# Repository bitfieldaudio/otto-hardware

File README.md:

# Description
otto-hw-beta is the hardware design for the OTTO beta circuit board. The design is implemented in KiCad.

# Target Outputs
By Beta formal release, the target output files will be the following:
Schematic
Layout
Fabrication Gerber
	Copper Layers
	Soldermask
	Silkscreen
	Drill
Assembly Gerber
	Paste Mask
	Component/Pin-XY Data
Bill of Materials
	Installed/Not-Installed
	Part Numbers
	Purchase Reference links
	Est. Cost

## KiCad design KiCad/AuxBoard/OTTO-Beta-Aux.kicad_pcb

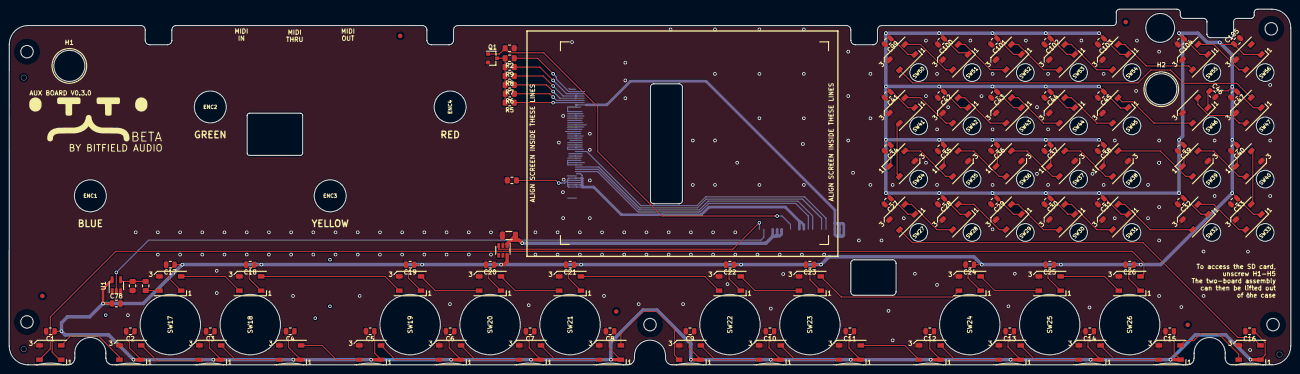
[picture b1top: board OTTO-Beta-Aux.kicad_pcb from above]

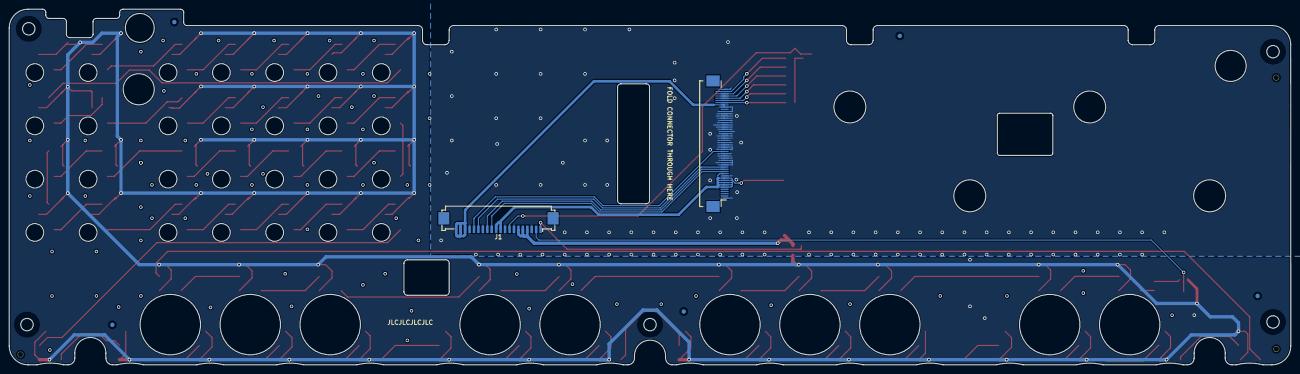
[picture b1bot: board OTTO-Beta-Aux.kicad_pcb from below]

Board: 2 copper layers, 288.5 x 80.1 mm, 187 parts (6 on the bottom side), 74 nets.

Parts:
C1, C2, C3, C4, C5, C6, C7, C8, C9, C10, C11, C12, C13, C14, C15, C16, C17, C18, C19, C20, C21, C22, C23, C24, C25, C26, C27, C28, C29, C30, C31, C32, C33, C34, C35, C36, C37, C38, C39, C40, C41, C42, C43, C44, C45, C46, C47, C78, C99, C100, C101, C102, C103, C104, C105: 100nF; C_0805_2012Metric
C48: 100nF; C_0805_2012Metric_Pad1.15x1.40mm_HandSolder
C49: 47uF; C_1206_3216Metric
ENC1, ENC2, ENC3, ENC4: ALPS EC11 HOLE; ALPS_EC11_aux_hole
FID2, FID3, FID4, FID5, FID6, FID8, FID9, FID10, FID11, FID12: Fiducial; Fiducial_1mm_Mask2mm
H1, H2: MountingHole_Pad; MountingHoleHole
H101, H102, H103: Tooling Hole; JLC_TOOLING_HOLE
H201, H202, H203, H204, H205: MountingHole; Mounting_Hole_M2.5_Loose_Fit
J1: Conn_01x20; X10B25L20T_FPC_1x20-1MP_P1.00mm_Horizontal
J1_KD028QVFMA17: Conn_02x25_Counter_Clockwise; F0501-B-50-20T-R
LED1, LED2, LED3, LED4, LED5, LED6, LED7, LED8, LED9, LED10, LED11, LED12, LED13, LED14, LED15, LED16, LED17, LED18, LED19, LED20, LED21, LED22, LED23, LED24, LED25, LED26, LED27, LED28, LED29, LED30, LED31, LED32, LED33, LED34, LED35, LED36, LED37, LED38, LED39, LED40, LED41, LED42, LED43, LED44, LED45, LED46, LED47, LED48, LED49, LED50, LED51, LED52, LED53, LED54: WS2812C; LED_WS2812B_PLCC4_5.0x5.0mm_P3.2mm
Q1: AO3400A; SOT-23
R1: 47k; R_0805_2012Metric_Pad1.15x1.40mm_HandSolder
R2, R5, R6, R7, R8, R9: 90; R_0805_2012Metric_Pad1.15x1.40mm_HandSolder
R11: 100k; R_0805_2012Metric_Pad1.15x1.40mm_HandSolder
R208: 100; R_0805_2012Metric_Pad1.15x1.40mm_HandSolder
SW17, SW18, SW19, SW20, SW21, SW22, SW23, SW24, SW25, SW26: ALPS SKHC Hole; ALPS_SKHC_aux_hole
SW27, SW28, SW29, SW30, SW31, SW32, SW33, SW34, SW35, SW36, SW37, SW38, SW39, SW40, SW41, SW42, SW43, SW44, SW45, SW46, SW47, SW50, SW51, SW52, SW53, SW54, SW55, SW56: 6x6x13mm Hole; 6x6mm_Switch_aux_hole
U1: SN74LV1T34_SOT-23_A; SOT-23-5_HandSoldering
U2: TPS22918_SOT23-6_A; SOT-23-6

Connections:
3V3: C48.1, J1.10, J1.11, J1_KD028QVFMA17.6, J1_KD028QVFMA17.7, J1_KD028QVFMA17.8, J1_KD028QVFMA17.9, J1_KD028QVFMA17.10, J1_KD028QVFMA17.12
+5V_LEDS: C1.1, C2.1, C3.1, C4.1, C5.1, C6.1, C7.1, C8.1, C9.1, C10.1, C11.1, C12.1, C13.1, C14.1, C15.1, C16.1, C17.1, C18.1, C19.1, C20.1, C21.1, C22.1, C23.1, C24.1, C25.1, C26.1, C27.1, C28.1, C29.1, C30.1, C31.1, C32.1, C33.1, C34.1, C35.1, C36.1, C37.1, C38.1, C39.1, C40.1, C41.1, C42.1, C43.1, C44.1, C45.1, C46.1, C47.1, C78.1, C99.1, C100.1, C101.1, C102.1, C103.1, C104.1, C105.1, LED1.1, LED2.1, LED3.1, LED4.1, LED5.1, LED6.1, LED7.1, LED8.1, LED9.1, LED10.1, LED11.1, LED12.1, LED13.1, LED14.1, LED15.1, LED16.1, LED17.1, LED18.1, LED19.1, LED20.1, LED21.1, LED22.1, LED23.1, LED24.1, LED25.1, LED26.1, LED27.1, LED28.1, LED29.1, LED30.1, LED31.1, LED32.1, LED33.1, LED34.1, LED35.1, LED36.1, LED37.1, LED38.1, LED39.1, LED40.1, LED41.1, LED42.1, LED43.1, LED44.1, LED45.1, LED46.1, LED47.1, LED48.1, LED49.1, LED50.1, LED51.1, LED52.1, LED53.1, LED54.1, U1.5, U2.6
+5V_RASPI: J1.18, J1.19, J1.20, J1_KD028QVFMA17.43
+5V_REG: C49.1, J1.4, J1.5, J1.6, U2.1
/LED_PWR_EN: J1.1, U2.3
/LEDs/LED_CONN1: LED1.4, LED26.2
/LEDs/LED_CONN2: LED16.2, LED27.4
/LEDs/LED_CONN3: LED47.2, LED48.4
/LEDs/LED_IN: LED17.4, R208.1
/LEDs/SPI_MOSI_MCU_5V: R11.1, R208.2, U1.4
/SPI_MOSI_MCU: J1.2, U1.2
BL_PWM: J1.8, Q1.1, R1.2
GND: C1.2, C2.2, C3.2, C4.2, C5.2, C6.2, C7.2, C8.2, C9.2, C10.2, C11.2, C12.2, C13.2, C14.2, C15.2, C16.2, C17.2, C18.2, C19.2, C20.2, C21.2, C22.2, C23.2, C24.2, C25.2, C26.2, C27.2, C28.2, C29.2, C30.2, C31.2, C32.2, C33.2, C34.2, C35.2, C36.2, C37.2, C38.2, C39.2, C40.2, C41.2, C42.2, C43.2, C44.2, C45.2, C46.2, C47.2, C48.2, C49.2, C78.2, C99.2, C100.2, C101.2, C102.2, C103.2, C104.2, C105.2, J1.3, J1.7, J1.9, J1.14, J1.17, J1_KD028QVFMA17.1, J1_KD028QVFMA17.11, J1_KD028QVFMA17.16, J1_KD028QVFMA17.17, J1_KD028QVFMA17.18, J1_KD028QVFMA17.19, J1_KD028QVFMA17.20, J1_KD028QVFMA17.21, J1_KD028QVFMA17.23, J1_KD028QVFMA17.24, J1_KD028QVFMA17.25, J1_KD028QVFMA17.26, J1_KD028QVFMA17.27, J1_KD028QVFMA17.28, J1_KD028QVFMA17.29, J1_KD028QVFMA17.30, J1_KD028QVFMA17.31, J1_KD028QVFMA17.32, J1_KD028QVFMA17.33, J1_KD028QVFMA17.34, J1_KD028QVFMA17.35, J1_KD028QVFMA17.36, J1_KD028QVFMA17.37, J1_KD028QVFMA17.38, J1_KD028QVFMA17.39, J1_KD028QVFMA17.40, J1_KD028QVFMA17.42, J1_KD028QVFMA17.50, LED1.3, LED2.3, LED3.3, LED4.3, LED5.3, LED6.3, LED7.3, LED8.3, LED9.3, LED10.3, LED11.3, LED12.3, LED13.3, LED14.3, LED15.3, LED16.3, LED17.3, LED18.3, LED19.3, LED20.3, LED21.3, LED22.3, LED23.3, LED24.3, LED25.3, LED26.3, LED27.3, LED28.3, LED29.3, LED30.3, LED31.3, LED32.3, LED33.3, LED34.3, LED35.3, LED36.3, LED37.3, LED38.3, LED39.3, LED40.3, LED41.3, LED42.3, LED43.3, LED44.3, LED45.3, LED46.3, LED47.3, LED48.3, LED49.3, LED50.3, LED51.3, LED52.3, LED53.3, LED54.3, Q1.2, R1.1, R11.2, U1.3, U2.2
unnamed: J1_KD028QVFMA17.44, R5.1
unnamed: J1_KD028QVFMA17.45, R6.1
unnamed: J1_KD028QVFMA17.46, R7.1
unnamed: J1_KD028QVFMA17.47, R8.1
unnamed: J1_KD028QVFMA17.48, R9.1
unnamed: J1_KD028QVFMA17.49, R2.1
unnamed: LED1.2, LED2.4
unnamed: LED2.2, LED3.4
unnamed: LED3.2, LED4.4
unnamed: LED4.2, LED5.4
unnamed: LED5.2, LED6.4
unnamed: LED6.2, LED7.4
unnamed: LED7.2, LED8.4
unnamed: LED8.2, LED9.4
unnamed: LED10.2, LED11.4
unnamed: LED9.2, LED10.4
unnamed: LED11.2, LED12.4
unnamed: LED12.2, LED13.4
unnamed: LED13.2, LED14.4
unnamed: LED14.2, LED15.4
unnamed: LED15.2, LED16.4
unnamed: LED17.2, LED18.4
unnamed: LED18.2, LED19.4
unnamed: LED19.2, LED20.4
unnamed: LED20.2, LED21.4
unnamed: LED21.2, LED22.4
unnamed: LED22.2, LED23.4
unnamed: LED23.2, LED24.4
unnamed: LED24.2, LED25.4
unnamed: LED25.2, LED26.4
unnamed: LED27.2, LED28.4
unnamed: LED28.2, LED29.4
unnamed: LED29.2, LED30.4
unnamed: LED30.2, LED31.4
unnamed: LED31.2, LED32.4
unnamed: LED32.2, LED33.4
unnamed: LED33.2, LED40.4
unnamed: LED34.2, LED41.4
unnamed: LED34.4, LED35.2
unnamed: LED35.4, LED36.2
unnamed: LED36.4, LED37.2
unnamed: LED37.4, LED38.2
unnamed: LED38.4, LED39.2
unnamed: LED39.4, LED40.2
unnamed: LED41.2, LED42.4
unnamed: LED42.2, LED43.4
unnamed: LED43.2, LED44.4
unnamed: LED44.2, LED45.4
unnamed: LED45.2, LED46.4
unnamed: LED46.2, LED47.4
unnamed: LED48.2, LED49.4
unnamed: LED49.2, LED50.4
unnamed: LED50.2, LED51.4
unnamed: LED51.2, LED52.4
unnamed: LED52.2, LED53.4
unnamed: LED53.2, LED54.4
unnamed: Q1.3, R2.2, R5.2, R6.2, R7.2, R8.2, R9.2
RESET: J1.12, J1_KD028QVFMA17.13
SPI_CS_RASPI: J1.13, J1_KD028QVFMA17.14
SPI_MOSI_RASPI: J1.16, J1_KD028QVFMA17.22
SPI_SCLK_RASPI: J1.15, J1_KD028QVFMA17.15

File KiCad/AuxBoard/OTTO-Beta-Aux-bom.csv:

Comment,Designator,Footprint,LCSC, AssemblyOption, JLCASM, MPN, LCSC PN
"100nF","C16,C15,C14,C13,C12,C11,C10,C9,C8,C7,C6,C5,C4,C3,C2,C1,C26,C25,C24,C23,C22,C21,C20,C19,C18,C17,C29,C30,C28,C33,C31,C32,C34,C46,C45,C47,C42,C41,C44,C43,C39,C38,C40,C35,C37,C36,C27,C78,C105,C104,C103,C102,C101,C100,C99","Capacitor_SMD:C_0805_2012Metric","","","BASIC","CC0805KRX7R9BB104","C49678"
"100nF","C48","Capacitor_SMD:C_0805_2012Metric_Pad1.15x1.40mm_HandSolder","","","BASIC","CC0805KRX7R9BB104","C49678"
"47uF","C49","Capacitor_SMD:C_1206_3216Metric","","","EXT","CL31A476MQHNNNE","C68361"
"10nF","C50","Capacitor_SMD:C_0805_2012Metric_Pad1.15x1.40mm_HandSolder","","","BASIC","CL21B103KBANNNC","C1710"
"ALPS EC11 HOLE","ENC1,ENC2,ENC4,ENC3","OTTO_Footprints_Lib:ALPS_EC11_aux_hole","","","N/A","N/A",""
"Fiducial","FID2,FID3,FID4,FID5,FID8,FID9,FID10,FID11,FID12,FID6","Fiducial:Fiducial_1mm_Mask2mm","","DNP","N/A","N/A",""
"Tooling Hole","H101,H102,H103","OTTO_Footprints_Lib:JLC_TOOLING_HOLE","","DNP","N/A","N/A",""
"MountingHole_Pad","H2,H1","OTTO_Footprints_Lib:MountingHoleHole","","DNP","N/A","N/A",""
"MountingHole","H201,H203,H205,H204,H202","OTTO_Footprints_Lib:Mounting_Hole_M2.5_Loose_Fit","","DNP","N/A","N/A",""
"Conn_01x20","J1","OTTO_Footprints_Lib:X10B25L20T_FPC_1x20-1MP_P1.00mm_Horizontal","","","DNP","X10B25L20T","C500179"
"Conn_02x25_Counter_Clockwise","J1_KD028QVFMA17","OTTO_Footprints_Lib:F0501-B-50-20T-R","","","DNP","F0501-B-50-20T-R","C481235"
"WS2812C","LED47,LED46,LED45,LED44,LED41,LED42,LED43,LED35,LED34,LED36,LED39,LED38,LED37,LED40,LED27,LED33,LED32,LED31,LED30,LED29,LED28,LED17,LED18,LED19,LED20,LED21,LED22,LED23,LED24,LED25,LED26,LED12,LED11,LED10,LED9,LED16,LED15,LED14,LED13,LED7,LED6,LED5,LED4,LED3,LED2,LED1,LED8,LED48,LED49,LED50,LED51,LED52,LED53,LED54","OTTO_Footprints_Lib:LED_WS2812B_PLCC4_5.0x5.0mm_P3.2mm","","","EXT","WS2812C","C114587"
"AO3400A","Q1","OTTO_Footprints_Lib:SOT-23","","","BASIC","AO3400A","C20917"
"47k","R1","Resistor_SMD:R_0805_2012Metric_Pad1.15x1.40mm_HandSolder","","","BASIC","0805W8F4702T5E","C17713"
"90","R2,R9,R8,R7,R6,R5","Resistor_SMD:R_0805_2012Metric_Pad1.15x1.40mm_HandSolder","","","EXT","0805W8F900JT5E","C247027"
"100","R208","Resistor_SMD:R_0805_2012Metric_Pad1.15x1.40mm_HandSolder","","","BASIC","0805W8F1000T5E","C17408"
"100k","R3,R11","Resistor_SMD:R_0805_2012Metric_Pad1.15x1.40mm_HandSolder","","","BASIC","0805W8F1003T5E","C17407"
"0","R4","Resistor_SMD:R_0805_2012Metric_Pad1.15x1.40mm_HandSolder","","","BASIC","0805W8F0000T5E","C17477"
"ALPS SKHC Hole","SW17,SW1,SW18,SW19,SW20,SW21,SW2,SW22,SW23,SW24,SW25,SW26,SW3,SW4,SW5,SW6,SW7,SW8,SW9,SW10,SW11,SW12,SW13,SW14,SW15,SW16","OTTO_Footprints_Lib:ALPS_SKHC_aux_hole","","","N/A","",""
"6x6x13mm Hole","SW41,SW34,SW27,SW42,SW35,SW28,SW43,SW36,SW29,SW44,SW37,SW30,SW45,SW38,SW31,SW46,SW39,SW32,SW47,SW40,SW33,SW50,SW51,SW52,SW53,SW54,SW55,SW56","OTTO_Footprints_Lib:6x6mm_Switch_aux_hole","","","N/A","",""
"SN74LV1T34_SOT-23_A","U1","OTTO_Footprints_Lib:SOT-23-5_HandSoldering","","","EXT","SN74LV1T34DBVR","C100024"
"TPS22918_SOT23-6_A","U2","OTTO_Footprints_Lib:SOT-23-6","","","EXT","TPS22918DBVR","C131941"

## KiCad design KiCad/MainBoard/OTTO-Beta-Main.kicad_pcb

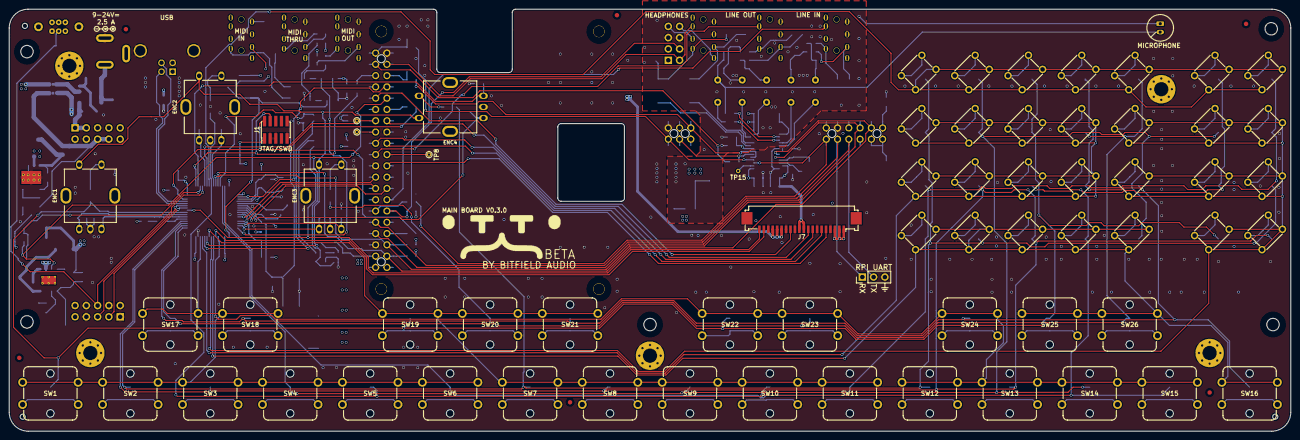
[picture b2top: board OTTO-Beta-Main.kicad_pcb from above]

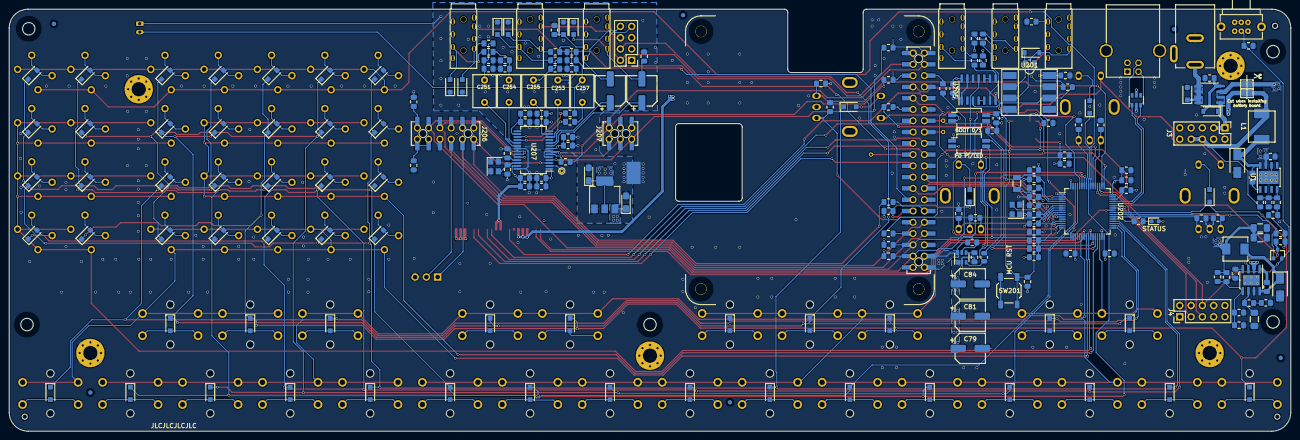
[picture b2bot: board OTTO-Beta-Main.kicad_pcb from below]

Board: 4 copper layers, 288.5 x 95.0 mm, 314 parts (230 on the bottom side), 199 nets.

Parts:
C1, C3, C243, C246, C247, C250, C260, C261, C264: 10uF; C_0805_2012Metric_Pad1.15x1.40mm_HandSolder
C2, C5, C6, C87: 10nF; C_0805_2012Metric_Pad1.15x1.40mm_HandSolder
C4, C7, C48, C49, C50, C51, C52, C53, C54, C55, C60, C61, C62, C63, C64, C65, C66, C67, C68, C69, C70, C71, C72, C73, C74, C98: 100nF; C_0805_2012Metric_Pad1.15x1.40mm_HandSolder
C8: 1nF; C_0805_2012Metric_Pad1.15x1.40mm_HandSolder
C9, C10, C11: 47uF; C_1206_3216Metric_Pad1.42x1.75mm_HandSolder
C79, C81, C84, C258, C262: 220uF; CP_Elec_6.3x4.5
C96, C97: 15pF; C_0805_2012Metric_Pad1.15x1.40mm_HandSolder
C204, C205, C265, C266: 30pF; C_0805_2012Metric_Pad1.15x1.40mm_HandSolder
C211: 4.7uF; C_0805_2012Metric_Pad1.15x1.40mm_HandSolder
C218, C219: 1uF; C_0805_2012Metric_Pad1.15x1.40mm_HandSolder
C251, C253, C254, C255, C257: 1uF (AUDIO); C_Rect_L7.2mm_W5.0mm_P5.00mm_FKS2_FKP2_MKS2_MKP2
C252, C256, C259: 220pF (C0G); C_0805_2012Metric_Pad1.15x1.40mm_HandSolder
C267, C268: 10uf Tantalum; CP_EIA-3216-18_Kemet-A_Pad1.58x1.35mm_HandSolder
D1, D2, D3, D4, D5, D6, D7, D8, D9, D10, D11, D12, D13, D14, D15, D16, D17, D18, D19, D20, D21, D22, D23, D24, D25, D26, D27, D28, D29, D30, D31, D32, D33, D34, D35, D36, D37, D38, D39, D40, D41, D42, D43, D44, D45, D46, D47, D58, D59, D60, D61, D62, D63, D64, D202, D203, D204, D205: SM4007PL; D_SOD-123F
D48: 15V BI TVS; D_SOD-123F
D49: 15V ZENER; D_SOD-123
D50, D51, D52, D53, D55, D56: 6V BI TVS; D_SOD-123F
D54, D65: SS34; D_SMA
D57: RED LED; LED_0603_1608Metric
D206: 1N4148W; D_SOD-123
DC201: Barrel Jack, 2.0mmID, 6.5mmOD; BarrelJack_2.0mmID_6.5mmOD
ENC1, ENC2, ENC3, ENC4: ALPS EC11E183440C; ALPS_EC11
FID1, FID2, FID3, FID4, FID5, FID6, FID7, FID8, FID9, FID10, FID11, FID12: Fiducial; Fiducial_1mm_Mask2mm
H1, H2, H3, H4, H5: MountingHole_Pad; MountingHole_3.2mm_M3_Pad_Via
H101, H102, H103: Tooling Hole; JLC_TOOLING_HOLE
H201, H202, H203, H204, H205: MountingHole; Mounting_Hole_M2.5_Loose_Fit
J1: Conn_ARM_JTAG_SWD_10; PinHeader_2x05_P1.27mm_Vertical_SMD
J2: Conn_02x04; PinHeader_2x04_P2.54mm_Vertical
J3, J4: Conn_02x05; PinHeader_2x05_P2.54mm_Vertical
J7: Conn_01x20; X10B25L20T_FPC_1x20-1MP_P1.00mm_Horizontal
J9: Conn_01x03; PinHeader_1x03_P2.54mm_Vertical
J201: Raspberry Pi Connector; Raspberry_Pi_A_FacingDown_TH
J206: Conn_02x06; Harwin_M20-7810645_2x06_P2.54mm_Vertical_SolderHoles
J207: Conn_02x03; Harwin_M20-7810345_2x03_P2.54mm_Vertical_SolderHoles
JP1, JP2: Jumper_2_Bridged; SolderJumper-2_P1.3mm_Bridged_Pad1.0x1.5mm
L1: 15uH; L_6.6x7.1
L2: 6.8uH; L_Sunlord_MWSA0518_5.4x5.2mm
MK201: Microphone; INGHAi_GMI6050p
NT1: Net-Tie_2; NetTie-2_Pad5.0mm
Q1: AO4407A; SOIC-8_3.9x4.9mm_P1.27mm
Q2: 2N7002; SOT-23
R1, R2, R3, R17, R19: 0; R_0805_2012Metric_Pad1.15x1.40mm_HandSolder
R4, R203, R204, R221, R225, R228, R229, R230: 47k; R_0805_2012Metric_Pad1.15x1.40mm_HandSolder
R5: 30k; R_0805_2012Metric_Pad1.15x1.40mm_HandSolder
R6, R7: 4.7K; R_0805_2012Metric_Pad1.15x1.40mm_HandSolder
R8: 68k; R_0805_2012Metric_Pad1.15x1.40mm_HandSolder
R9: 3.3k; R_0805_2012Metric_Pad1.15x1.40mm_HandSolder
R10: 12k; R_0805_2012Metric_Pad1.15x1.40mm_HandSolder
R11: 4.3k; R_0805_2012Metric_Pad1.15x1.40mm_HandSolder
R12: 180k; R_0805_2012Metric_Pad1.15x1.40mm_HandSolder
R13, R18, R20, R26: 100k; R_0805_2012Metric_Pad1.15x1.40mm_HandSolder
R14: 10k; R_0805_2012Metric_Pad1.15x1.40mm_HandSolder
R15: 13k; R_0805_2012Metric_Pad1.15x1.40mm_HandSolder
R16: 100k; R_0805_2012Metric
R28, R227: 330; R_0805_2012Metric_Pad1.15x1.40mm_HandSolder
R202, R205: 2.2k; R_0805_2012Metric_Pad1.15x1.40mm_HandSolder
R212, R214: 10; R_0805_2012Metric_Pad1.15x1.40mm_HandSolder
R213, R215, R231, R232, R233, R234: 33; R_0805_2012Metric_Pad1.15x1.40mm_HandSolder
R216: 270; R_0805_2012Metric_Pad1.15x1.40mm_HandSolder
R217: 220; R_0805_2012Metric_Pad1.15x1.40mm_HandSolder
R218, R219, R222, R224: 5.1k; R_0805_2012Metric_Pad1.15x1.40mm_HandSolder
R220, R223: 100; R_0805_2012Metric_Pad1.15x1.40mm_HandSolder
R226: 680; R_0805_2012Metric_Pad1.15x1.40mm_HandSolder
SW1, SW2, SW3, SW4, SW5, SW6, SW7, SW8, SW9, SW10, SW11, SW12, SW13, SW14, SW15, SW16: ALPS SKHC; ALPS_SKHC_white
SW17, SW18, SW19, SW20, SW21, SW22, SW23, SW24, SW25, SW26: ALPS SKHC; ALPS_SKHC_black
SW27, SW28, SW29, SW30, SW31, SW32, SW33, SW34, SW35, SW36, SW37, SW38, SW39, SW40, SW41, SW42, SW43, SW44, SW45, SW46, SW47, SW50, SW51, SW52, SW53, SW54, SW55, SW56: 6x6x13mm; 6x6mm_Switch
SW48, SW202: SW_DIP_x02; SW_DIP_SPSTx02_Slide_HRO_EP-02KS
SW49: SW_DPDT_x2; SSAC120100
SW201: 5.2x5.2x1.5mm; SW_SPST_5.2x5.2x1.5mm
TP2, TP7, TP8, TP15: TestPoint; TestPoint_THTPad_D1.0mm_Drill0.5mm
TRS201, TRS202, TRS203, TRS204, TRS205, TRS206: PJ-3930-8A; 3.5mm_jack_PJ-3930-8A
U1: TPS5430DDA; TI_SO-PowerPAD-8_ThermalVias
U2: TPS54331DR; SOIC-8-1EP_3.9x4.9mm_P1.27mm_EP2.41x3.81mm_ThermalVias
U5: TPS22918_SOT23-6_A; SOT-23-6
U201: 6N137; DIP-8_W8.89mm_SMDSocket_LongPads
U202: STM32F103R8T6; LQFP-64_10x10mm_P0.5mm
U204: SRV05-4; SOT-23-6
U205: SN74HC14; SOIC-14_3.9x8.7mm_P1.27mm
U207: WM8731; SSOP-28_5.3x10.2mm_P0.65mm
U208: AMS1117-3.3; SOT-223-3_TabPin2
USB201: USB_B
Y201: 16MHz; Crystal_SMD_3225-4Pin_3.2x2.5mm
Y202: 32.768kHz; Crystal_SMD_3215-2Pin_3.2x1.5mm_HandSoldering
Y203: 12.288MHz; Crystal_SMD_3225-4Pin_3.2x2.5mm

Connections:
+3V3A_MCU: C55.1, C219.1, R19.1, U202.13
+3V3_ANALOG: C72.1, C73.1, C246.2, C250.2, C268.1, U207.8, U207.14, U208.2
+3V3_MCU: C3.2, C10.1, C11.1, C49.1, C50.1, C51.1, C52.1, C53.1, C54.1, C211.1, C218.2, D57.2, J1.1, J4.9, J4.10, L2.2, R4.1, R6.1, R8.1, R10.1, R19.2, SW48.2, SW202.1, SW202.2, U202.1, U202.19, U202.32, U202.48, U202.64
+3V3_RASPI: C69.2, C70.1, C71.2, C243.2, C247.1, C260.2, J7.10, J7.11, J201.1, J201.17, J206.1, R202.1, R205.1, R213.1, R215.1, R216.1, U205.14, U207.1, U207.27
+5V_RASPI: C68.2, C261.2, C267.1, J7.1, J7.2, J7.3, J201.2, J201.4, J206.2, J206.4, R17.1, U5.6, U201.8, U208.3
+5V_REG: C5.1, C79.1, C81.1, C84.1, J2.1, J2.3, J3.5, J3.7, J7.15, J7.16, J7.17, JP2.2, R18.1, R20.1, SW48.1, U2.2, U5.1
/AUDIO/AMP_OUT_L: J2.8, TRS206.TS
/AUDIO/AMP_OUT_R: J2.7, TRS206.R1S
/AUDIO/CODEC_CLKOUT: TP15.1, U207.2
/AUDIO/HP_OUT_L: C258.2, D56.2, R228.2, TRS206.T
/AUDIO/HP_OUT_R: C262.2, D55.2, R230.2, TRS206.R1
/AUDIO/I2S_BCLK*: J206.12, R231.2, U207.3
/AUDIO/I2S_DIN*: J207.4, R233.2, U207.6
/AUDIO/I2S_DOUT*: J207.6, R234.2, U207.4
/AUDIO/I2S_LRCLK*: J207.1, R232.2, U207.5, U207.7
/AUDIO/LINE_IN_L: D51.2, R218.2, TRS204.T
/AUDIO/LINE_IN_R: D50.2, R222.2, TRS204.R1
/AUDIO/LINE_OUT_L: D53.2, R220.2, TRS205.T
/AUDIO/LINE_OUT_R: D52.2, R223.2, TRS205.R1
/AUDIO/MIC_IN: C257.2, C259.1, MK201.2, R226.2, R229.2
/CE1_GPIO7_RASPI: J201.26, TP2.1
/GPIO1_RASPI: J201.28, TP7.1, U202.54
/ICP_RST: C48.2, J1.10, R3.1, R4.2, SW201.1, U202.7
/ICP_SWCLK: J1.4, R2.1, R7.1, U202.49
/ICP_SWDIO: J1.2, R1.2, R6.2, U202.46
/MCU/+5V_USB: J3.9, J3.10, U204.5, USB201.1
/MCU/BARREL_IN: D49.1, J3.1, J3.3, JP1.1, Q1.1, Q1.2, Q1.3
/MCU/BOOT0: R203.2, SW202.4, U202.60
/MCU/BOOT1: R204.2, SW202.3, U202.28
/MCU/BUCK_IN: C1.2, J3.2, J3.4, JP1.2, U1.7
/MCU/BUCK_OUT: J3.6, J3.8, JP2.1, L1.2, R14.1
/MCU/COL_1: SW1.2, SW2.2, SW3.2, SW4.2, SW5.2, SW6.2, SW17.2, SW18.2, U202.30
/MCU/COL_2: SW7.2, SW8.2, SW9.2, SW10.2, SW11.2, SW19.2, SW20.2, SW21.2, U202.26
/MCU/COL_3: SW12.2, SW13.2, SW14.2, SW15.2, SW22.2, SW23.2, SW24.2, U202.22
/MCU/COL_4: SW16.2, SW25.2, SW26.2, SW27.2, SW28.2, SW29.2, SW30.2, SW31.2, U202.24
/MCU/COL_5: SW32.2, SW33.2, SW38.2, SW39.2, SW40.2, SW45.2, SW46.2, SW47.2, U202.25
/MCU/COL_6: SW34.2, SW35.2, SW36.2, SW37.2, SW41.2, SW42.2, SW43.2, SW44.2, U202.29
/MCU/COL_7: ENC1.S1, ENC2.S1, ENC3.S1, ENC4.S1, U202.27
/MCU/COL_8: SW50.2, SW51.2, SW52.2, SW53.2, SW54.2, SW55.2, SW56.2, U202.55
/MCU/ENC_A_1: C60.1, ENC1.A, U202.39
/MCU/ENC_A_2: C62.1, ENC2.A, U202.53
/MCU/ENC_A_3: C64.1, ENC3.A, U202.15
/MCU/ENC_A_4: C66.1, ENC4.A, U202.8
/MCU/ENC_B_1: C61.2, ENC1.B, U202.38
/MCU/ENC_B_2: C63.2, ENC2.B, U202.57
/MCU/ENC_B_3: C65.2, ENC3.B, U202.14
/MCU/ENC_B_4: C67.2, ENC4.B, U202.50
/MCU/OSC32_IN: C96.1, U202.3, Y202.2
/MCU/OSC32_OUT: C97.1, U202.4, Y202.1
/MCU/OSC_IN: C204.1, U202.5, Y201.3
/MCU/OSC_OUT: C205.1, U202.6, Y201.1
/MCU/PERIPHERALS/BARL: D48.1, DC201.1, Q1.5, Q1.6, Q1.7, Q1.8
/MCU/PERIPHERALS/PI_PWR_EN_OVERRIDE: R16.2, SW48.4
/MCU/PROG_UART_RX: J4.5, U202.43
/MCU/PROG_UART_TX: J4.3, U202.42
/MCU/ROW_1: D1.1, D19.1, D22.1, D25.1, D32.1, D43.1, D60.1, D202.1, U202.40
/MCU/ROW_2: D17.1, D20.1, D23.1, D26.1, D44.1, D45.1, D62.1, D203.1, U202.33
/MCU/ROW_3: D16.1, D18.1, D21.1, D24.1, D37.1, D38.1, D61.1, U202.34
/MCU/ROW_4: D2.1, D7.1, D12.1, D28.1, D40.1, D41.1, D58.1, D205.1, U202.35
/MCU/ROW_5: D3.1, D8.1, D13.1, D29.1, D33.1, D35.1, U202.36
/MCU/ROW_6: D4.1, D9.1, D14.1, D31.1, D42.1, D46.1, D59.1, U202.61
/MCU/ROW_7: D5.1, D10.1, D15.1, D30.1, D36.1, D39.1, D63.1, D204.1, U202.56
/MCU/ROW_8: D6.1, D11.1, D27.1, D34.1, D47.1, D64.1, U202.62
/MCU/STATUS_LED: R28.1, U202.37
/MCU/USBD_N: U202.44, U204.3, USB201.2
/MCU/USBD_P: U202.45, U204.1, USB201.3
/PWM1_GPIO13_RASPI: J201.33, U202.2
/SPI_MISO_RASPI: J201.21, TP8.1
AMP_ENABLE: J2.4, J201.11, R26.1
BL_PWM: J7.13, J201.32
DISPLAY_RESET: J7.9, J201.27
GND: C1.1, C3.1, C4.2, C5.2, C6.2, C9.2, C10.2, C11.2, C48.1, C49.2, C50.2, C51.2, C52.2, C53.2, C54.2, C55.2, C60.2, C61.1, C62.2, C63.1, C64.2, C65.1, C66.2, C67.1, C68.1, C69.1, C70.2, C71.1, C79.2, C81.2, C84.2, C87.2, C96.2, C97.2, C98.1, C204.2, C205.2, C211.2, C218.1, C219.2, C243.1, C247.2, C260.1, C261.1, C265.2, C266.2, D48.2, D54.2, D65.2, DC201.2, ENC1.C, ENC2.C, ENC3.C, ENC4.C, H1.1, H2.1, H3.1, H4.1, H5.1, J1.3, J1.5, J1.9, J4.1, J4.2, J4.4, J4.7, J4.8, J7.4, J7.7, J7.12, J7.14, J7.18, J9.3, J201.6, J201.9, J201.14, J201.20, J201.25, J201.30, J201.34, J201.39, J206.6, J206.9, J207.5, NT1.2, R5.2, R7.2, R9.2, R11.2, R12.2, R13.2, R15.2, R26.2, R203.1, R204.1, SW49.1, SW201.2, TRS201.R2, TRS201.S, TRS202.R2, TRS202.S, U1.6, U1.9, U2.7, U5.2, U201.5, U202.12, U202.18, U202.20, U202.31, U202.47, U202.63, U204.2, U205.1, U205.7, U205.13, U207.21, U207.22, U207.28, USB201.4, USB201.5, Y201.2, Y201.4, Y203.2, Y203.4
GNDA: C72.2, C73.2, C74.2, C246.1, C250.1, C252.2, C256.2, C259.2, C264.1, C267.2, C268.2, D50.1, D51.1, D52.1, D53.1, D55.1, D56.1, J2.5, J2.6, MK201.1, NT1.1, R219.2, R221.1, R224.2, R225.1, R228.1, R229.1, R230.1, TRS204.R2, TRS204.S, TRS205.R2, TRS205.S, TRS206.R2, TRS206.S, U207.11, U207.15, U208.1
HP_SENSE: J2.2, J201.37, TRS206.R2S
I2C_SCL: J201.5, J206.5, R202.2, U202.58, U207.24
I2C_SDA: J201.3, J206.3, R205.2, U202.59, U207.23
I2S_BCLK: J201.12, R231.1
I2S_DIN: J201.38, R233.1
I2S_DOUT: J201.40, R234.1
I2S_LRCLK: J201.35, R232.1
LED_PWR_EN: J7.20, SW48.3, U202.41
LI_SENSE: J201.13, TRS204.R2S
LO_SENSE: J201.22, TRS205.R2S
MIDI_IN: R216.2, U201.6, U202.17, U205.3
MIDI_OUT: U202.16, U205.11
unnamed: C2.1, D65.1, L1.1, U1.8
unnamed: C2.2, U1.1
unnamed: C6.1, U2.4
unnamed: C7.1, D54.1, L2.1, U2.8
unnamed: C7.2, U2.1
unnamed: C8.1, C9.1, U2.6
unnamed: C8.2, R5.1
unnamed: C87.1, U5.4
unnamed: C98.2, TRS203.S
unnamed: C251.1, U207.20
unnamed: C251.2, C252.1, R218.1, R219.1
unnamed: C253.1, R220.1, R221.2
unnamed: C253.2, U207.12
unnamed: C254.1, U207.19
unnamed: C254.2, C256.1, R222.1, R224.1
unnamed: C255.1, R223.1, R225.2
unnamed: C255.2, U207.13
unnamed: C257.1, R227.2
unnamed: C258.1, U207.9
unnamed: C262.1, U207.10
unnamed: C74.1, C264.2, U207.16
unnamed: C265.1, U207.25, Y203.1
unnamed: C266.1, U207.26, Y203.3
unnamed: D1.2, SW1.1
unnamed: D2.2, SW2.1
unnamed: D3.2, SW3.1
unnamed: D4.2, SW4.1
unnamed: D5.2, SW5.1
unnamed: D6.2, SW6.1
unnamed: D7.2, SW7.1
unnamed: D8.2, SW8.1
unnamed: D9.2, SW9.1
unnamed: D10.2, SW10.1
unnamed: D11.2, SW11.1
unnamed: D12.2, SW12.1
unnamed: D13.2, SW13.1
unnamed: D14.2, SW14.1
unnamed: D15.2, SW15.1
unnamed: D16.2, SW16.1
unnamed: D17.2, SW17.1
unnamed: D18.2, SW18.1
unnamed: D19.2, SW19.1
unnamed: D20.2, SW20.1
unnamed: D21.2, SW21.1
unnamed: D22.2, SW22.1
unnamed: D23.2, SW23.1
unnamed: D24.2, SW24.1
unnamed: D25.2, SW25.1
unnamed: D26.2, SW26.1
unnamed: D27.2, SW27.1
unnamed: D28.2, SW28.1
unnamed: D29.2, SW29.1
unnamed: D30.2, SW30.1
unnamed: D31.2, SW31.1
unnamed: D32.2, SW32.1
unnamed: D33.2, SW33.1
unnamed: D34.2, SW34.1
unnamed: D35.2, SW35.1
unnamed: D36.2, SW36.1
unnamed: D37.2, SW37.1
unnamed: D38.2, SW38.1
unnamed: D39.2, SW39.1
unnamed: D40.2, SW40.1
unnamed: D41.2, SW41.1
unnamed: D42.2, SW42.1
unnamed: D43.2, SW43.1
unnamed: D44.2, SW44.1
unnamed: D45.2, SW45.1
unnamed: D46.2, SW46.1
unnamed: D47.2, SW47.1
unnamed: D49.2, Q1.4, R13.1
unnamed: D57.1, R28.2
unnamed: D58.2, SW50.1
unnamed: D59.2, SW51.1
unnamed: D60.2, SW52.1
unnamed: D61.2, SW53.1
unnamed: D62.2, SW54.1
unnamed: D63.2, SW55.1
unnamed: D64.2, SW56.1
unnamed: D202.2, ENC1.S2
unnamed: D203.2, ENC3.S2
unnamed: D204.2, ENC2.S2
unnamed: D205.2, ENC4.S2
unnamed: D206.1, R217.1, U201.2
unnamed: D206.2, TRS203.T, U201.3
unnamed: J201.7, R3.2
unnamed: J201.29, R1.1
unnamed: J201.36, R2.2
unnamed: R8.2, R9.1, R10.2, R12.1, U2.5
unnamed: R11.1, R14.2, R15.1, U1.4
unnamed: R17.2, U5.5
unnamed: R212.1, U205.8
unnamed: R212.2, TRS201.T
unnamed: R213.2, TRS201.R1
unnamed: R214.1, U205.6
unnamed: R214.2, TRS202.T
unnamed: R215.2, TRS202.R1
unnamed: R217.2, TRS203.R1
unnamed: R226.1, U207.17
unnamed: R227.1, U207.18
unnamed: U205.4, U205.5
unnamed: U205.9, U205.10
PI_PWR_EN: J201.31, Q2.3, R16.1, R20.2, U2.3, U5.3
PWR_BUTTON: C4.1, J4.6, Q2.2, SW49.2, U202.52
PWR_HOLD: Q2.1, R18.2, U202.51
RPI_UART_RX: J9.1, J201.10, J206.10
RPI_UART_TX: J9.2, J201.8, J206.8
SPI_CS_RASPI_DISPLAY: J7.8, J201.24
SPI_MOSI_MCU: J7.19, U202.23
SPI_MOSI_RASPI: J7.5, J201.19
SPI_SCLK_RASPI: J7.6, J201.23
TRIGGER1: J201.15, U202.9
TRIGGER2: J201.16, U202.10
TRIGGER3: J201.18, U202.11

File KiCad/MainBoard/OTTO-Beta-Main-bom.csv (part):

Comment,Designator,Footprint,LCSC, JLCASM, MPN, LCSC PN
"4.7uF","C211","Capacitor_SMD:C_0805_2012Metric_Pad1.15x1.40mm_HandSolder","","BASIC","CL21A475KAQNNNE","C1779"
"1uF","C219,C218","Capacitor_SMD:C_0805_2012Metric_Pad1.15x1.40mm_HandSolder","","BASIC","CL21B105KBFNNNE","C28323"
"10uF","C246,C250,C264,C247,C243,C261,C260,C3,C1","Capacitor_SMD:C_0805_2012Metric_Pad1.15x1.40mm_HandSolder","","BASIC","CL21A106KAYNNNE","C15850"
"1uF (AUDIO)","C254,C251,C253,C255,C257","OTTO_Footprints_Lib:C_Rect_L7.2mm_W5.0mm_P5.00mm_FKS2_FKP2_MKS2_MKP2","","DNP","MKS2C041001F00JSSD","C92673"
"220pF (C0G)","C256,C252,C259","Capacitor_SMD:C_0805_2012Metric_Pad1.15x1.40mm_HandSolder","","BASIC","CL21B221KBANNNC","C53172"
"220uF","C262,C258,C84,C81,C79","OTTO_Footprints_Lib:CP_Elec_6.3x4.5","","EXT","OVZ221M0JTR-0604","C250096"
"30pF","C265,C266,C205,C204","Capacitor_SMD:C_0805_2012Metric_Pad1.15x1.40mm_HandSolder","","BASIC","CL21C300JBANNNC","C1809"
"10uf Tantalum","C268,C267","OTTO_Footprints_Lib:CP_EIA-3216-18_Kemet-A_Pad1.58x1.35mm_HandSolder","","BASIC","TAJA106K016RNJ","C7171"
"100nF","C72,C73,C74,C71,C70,C69,C68,C98,C49,C50,C51,C52,C55,C48,C53,C54,C60,C61,C62,C63,C64,C65,C66,C67,C7,C4","Capacitor_SMD:C_0805_2012Metric_Pad1.15x1.40mm_HandSolder","","BASIC","CC0805KRX7R9BB104","C49678"
"1nF","C8","Capacitor_SMD:C_0805_2012Metric_Pad1.15x1.40mm_HandSolder","","BASIC","CL21B102KBCNNNC","C46653"
"10nF","C87,C2,C5,C6","Capacitor_SMD:C_0805_2012Metric_Pad1.15x1.40mm_HandSolder","","BASIC","CL21B103KBANNNC","C1710"
"47uF","C9,C10,C11","Capacitor_SMD:C_1206_3216Metric_Pad1.42x1.75mm_HandSolder","","BASIC","CL31A476MPHNNNE","C96123"
"15pF","C96,C97","Capacitor_SMD:C_0805_2012Metric_Pad1.15x1.40mm_HandSolder","","BASIC","CL21C150JBANNNC","C1794"
"SM4007PL","D1,D3,D4,D5,D6,D7,D8,D9,D10,D11,D12,D13,D14,D15,D16,D17,D18,D19,D20,D21,D22,D23,D24,D25,D26,D27,D34,D41,D33,D47,D40,D32,D46,D39,D31,D45,D38,D30,D44,D37,D29,D43,D36,D28,D42,D35,D202,D204,D203,D205,D2,D58,D64,D63,D62,D61,D60,D59","Diode_SMD:D_SOD-123F","","BASIC","SM4007PL","C64898"
"1N4148W","D206","Diode_SMD:D_SOD-123","","BASIC","1N4148W","C81598"
"15V BI TVS","D48","Diode_SMD:D_SOD-123F","","EXT","SMF15CA","C123803"
"15V ZENER","D49","Diode_SMD:D_SOD-123","","EXT","BZT52C15","C173427"
"6V BI TVS","D51,D53,D56,D55,D52,D50","Diode_SMD:D_SOD-123F","","EXT","SMF6.0CA","C123791"
"RED LED","D57","LED_SMD:LED_0603_1608Metric","","BASIC","KT-0603R","C2286"
"SS34","D65,D54","Diode_SMD:D_SMA","","BASIC","SS34","C8678"
"Barrel Jack, 2.0mmID, 6.5mmOD","DC201","OTTO_Footprints_Lib:BarrelJack_2.0mmID_6.5mmOD","","DNP","DC-005 5.5-2.0MM","C16214"
"ALPS EC11E183440C","ENC1,ENC2,ENC3,ENC4","OTTO_Footprints_Lib:ALPS_EC11","","DNP","EC11E183440C","C370986"
"Fiducial","FID1,FID2,FID3,FID4,FID5,FID7,FID8,FID9,FID10,FID11,FID6,FID12","Fiducial:Fiducial_1mm_Mask2mm","","N/A","N/A",""
"Tooling Hole","H101,H102,H103","OTTO_Footprints_Lib:JLC_TOOLING_HOLE","","N/A","N/A",""
"MountingHole","H203,H201,H204,H202,H205","OTTO_Footprints_Lib:Mounting_Hole_M2.5_Loose_Fit","","N/A","N/A",""
"MountingHole_Pad","H4,H3,H1,H5,H2","MountingHole:MountingHole_3.2mm_M3_Pad_Via","","N/A","N/A",""
"Conn_ARM_JTAG_SWD_10","J1","Connector_PinHeader_1.27mm:PinHeader_2x05_P1.27mm_Vertical_SMD","","DNP","20021111-00010T4LF","C239059"
"Conn_02x04","J2","Connector_PinHeader_2.54mm:PinHeader_2x04_P2.54mm_Vertical","","N/A","N/A",""
"Raspberry Pi Connector","J201","OTTO_Footprints_Lib:Raspberry_Pi_A_FacingDown_TH","","N/A","M20-7812045",""
"Conn_02x06","J206","OTTO_Footprints_Lib:Harwin_M20-7810645_2x06_P2.54mm_Vertical_SolderHoles","","N/A","M20-7810645",""
"Conn_02x03","J207","OTTO_Footprints_Lib:Harwin_M20-7810345_2x03_P2.54mm_Vertical_SolderHoles","","N/A","M20-7810345",""
"Conn_02x05","J3,J4","Connector_PinHeader_2.54mm:PinHeader_2x05_P2.54mm_Vertical","","DNP","N/A","C124355"
"Conn_01x20","J7","OTTO_Footprints_Lib:X10B25L20T_FPC_1x20-1MP_P1.00mm_Horizontal","","DNP","","C124357"
"Conn_01x03","J9","Connector_PinHeader_2.54mm:PinHeader_1x03_P2.54mm_Vertical","","DNP","","C225478"
"Jumper_2_Bridged","JP1,JP2","Jumper:SolderJumper-2_P1.3mm_Bridged_Pad1.0x1.5mm",""
"15uH","L1","OTTO_Footprints_Lib:L_6.6x7.1","","EXTDNP","MWSA0603-150MT","C132136"
"6.8uH","L2","Inductor_SMD:L_Sunlord_MWSA0518_5.4x5.2mm","","EXTDNP","SLO0530H6R8MTT","C325965"
"Microphone","MK201","OTTO_Footprints_Lib:INGHAi_GMI6050p","","DNP","GMI6050P-42db","C233942"
"Net-Tie_2","NT1","OTTO_Footprints_Lib:NetTie-2_Pad5.0mm","","N/A","N/A",""
"AO4407A","Q1","OTTO_Footprints_Lib:SOIC-8_3.9x4.9mm_P1.27mm","","BASIC","AO4407A","C16072"
"2N7002","Q2","Package_TO_SOT_SMD:SOT-23","","BASIC","2N7002","C8545"
"12k","R10","Resistor_SMD:R_0805_2012Metric_Pad1.15x1.40mm_HandSolder","","BASIC","0805W8F1202T5E","C17444"
"4.3k","R11","Resistor_SMD:R_0805_2012Metric_Pad1.15x1.40mm_HandSolder","","BASIC","0805W8F4301T5E","C17667"
"180k","R12","Resistor_SMD:R_0805_2012Metric_Pad1.15x1.40mm_HandSolder","","BASIC","0805W8F1803T5E","C17501"
"10k","R14","Resistor_SMD:R_0805_2012Metric_Pad1.15x1.40mm_HandSolder","","BASIC","0805W8F1002T5E","C17414"
"13k","R15","Resistor_SMD:R_0805_2012Metric_Pad1.15x1.40mm_HandSolder","","BASIC","0805W8F1302T5E","C17455"
"100k","R16","Resistor_SMD:R_0805_2012Metric","","BASIC","0805W8F1003T5E","C17407"
"2.2k","R202,R205","Resistor_SMD:R_0805_2012Metric_Pad1.15x1.40mm_HandSolder","","BASIC","0805W8F2201T5E","C17520"
"10","R212,R214","Resistor_SMD:R_0805_2012Metric_Pad1.15x1.40mm_HandSolder","","BASIC","0805W8F100JT5E","C17415"
"270","R216","Resistor_SMD:R_0805_2012Metric_Pad1.15x1.40mm_HandSolder","","BASIC","0805W8F2700T5E","C17590"
"220","R217","Resistor_SMD:R_0805_2012Metric_Pad1.15x1.40mm_HandSolder","","BASIC","0805W8F2200T5E","C17557"
"47k","R221,R225,R229,R230,R228,R204,R203,R4","Resistor_SMD:R_0805_2012Metric_Pad1.15x1.40mm_HandSolder","","BASIC","0805W8F4702T5E","C17713"
"5.1k","R222,R224,R218,R219","Resistor_SMD:R_0805_2012Metric_Pad1.15x1.40mm_HandSolder","","BASIC","0805W8F5101T5E","C27834"
"100","R223,R220","Resistor_SMD:R_0805_2012Metric_Pad1.15x1.40mm_HandSolder","","BASIC","0805W8F1000T5E","C17408"
"680","R226","Resistor_SMD:R_0805_2012Metric_Pad1.15x1.40mm_HandSolder","","BASIC","0805W8F6800T5E","C17798"
"330","R227,R28","Resistor_SMD:R_0805_2012Metric_Pad1.15x1.40mm_HandSolder","","BASIC","0805W8F3300T5E","C17630"
"33","R231,R232,R233,R234,R213,R215","Resistor_SMD:R_0805_2012Metric_Pad1.15x1.40mm_HandSolder","","BASIC","0805W8F330JT5E","C17634"
"100k","R26,R13,R18,R20","Resistor_SMD:R_0805_2012Metric_Pad1.15x1.40mm_HandSolder","","BASIC","0805W8F1003T5E","C17407"
"0","R3,R2,R1,R19,R17","Resistor_SMD:R_0805_2012Metric_Pad1.15x1.40mm_HandSolder","","BASIC","0805W8F0000T5E","C17477"
"30k","R5","Resistor_SMD:R_0805_2012Metric_Pad1.15x1.40mm_HandSolder","","BASIC","0805W8F3002T5E","C17621"
"4.7K","R6,R7","Resistor_SMD:R_0805_2012Metric_Pad1.15x1.40mm_HandSolder","","BASIC","0805W8F4701T5E","C17673"
"68k","R8","Resistor_SMD:R_0805_2012Metric_Pad1.15x1.40mm_HandSolder","","BASIC","0805W8F6802T5E","C17801"
"3.3k","R9","Resistor_SMD:R_0805_2012Metric_Pad1.15x1.40mm_HandSolder","","BASIC","0805W8F3301T5E","C26010"
"ALPS SKHC","SW1,SW2,SW3,SW4,SW5,SW6,SW7,SW8,SW9,SW10,SW11,SW12,SW13,SW14,SW15,SW16","OTTO_Footprints_Lib:ALPS_SKHC_white","","DNP","SKHCBGA010","C139753"
"ALPS SKHC","SW17,SW18,SW19,SW20,SW21,SW22,SW23,SW24,SW25,SW26","OTTO_Footprints_Lib:ALPS_SKHC_black","","DNP","SKHCBGA010","C139753"
"5.2x5.2x1.5mm","SW201","OTTO_Footprints_Lib:SW_SPST_5.2x5.2x1.5mm","","EXTDNP","TS-1187A-B-A-B","C318884"
"SW_DIP_x02","SW202,SW48","OTTO_Footprints_Lib:SW_DIP_SPSTx02_Slide_HRO_EP-02KS","","DNP","EP-02KS","C129087"
"6x6x13mm","SW41,SW34,SW27,SW42,SW35,SW28,SW43,SW36,SW29,SW44,SW37,SW30,SW45,SW38,SW31,SW46,SW39,SW32,SW47,SW40,SW33,SW50,SW51,SW52,SW53,SW54,SW55,SW56","OTTO_Footprints_Lib:6x6mm_Switch","","DNP","K2-1102DP-S3SW-04","C136674"
"SW_DPDT_x2","SW49","OTTO_Footprints_Lib:SSAC120100","","DNP","SSAC120100","C202374"
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
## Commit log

2019-11-30 initial commit of schematic from Bastian
2019-11-30 add cached symbols to local library
2019-12-03 PWR entry, ESD, JTAG, PU/PDs modified. Review pass 1
2019-12-03 add LICENSE and README
2019-12-03 create folder structure
2019-12-03 Add 3D folder
2019-12-10 roll in changes from Bastian
2019-12-15 added buck/boost power supply for 5V rail
2019-12-31 added power switching and extra pulls for programming lines
2019-12-31 connected unconnected signals and MIDI to spare MCU UART
2020-01-02 add all resistor part numbers and create footprint library
2020-01-04 added part numbers for capacitors and crystals
2020-01-06 more part numbers added: audio caps
2020-01-07 add more part numbers, samtec connector footprint
2020-01-08 add switch and encoder parts. BM Complete. Footprints complete.
2020-01-10 add BOM scripts, fix schematic hierarchy
2020-01-11 Add power switch and other misc nice to haves
2020-01-11 Fixes for external battery board and Routing started
2020-01-11 Add SP3T style DP3T footprint and some schematic labels
2020-01-11 fix electrical rules check errors
2020-01-13 routed buck boost supply
2020-01-14 routed 3v3 and power switches
2020-01-18 add fault/status LED to MCU
2020-01-21 more power supply routing and stm32 placement
2020-01-23 routed mcu decoupling
2020-01-24 fix peripheral connections and route more critical components
2020-01-26 routed audio
2020-01-26 add 3215 crystal footprint
2020-01-29 Placement of all components
2020-01-30 change mcu reset button and route more stuff
2020-02-08 add analog ground layout
2020-02-08 misc raspi routing
2020-02-19 started kay matrix routing
2020-02-19 key matrix routed (but untidy), added cutout for CPU heatsink
2020-02-20 Add and route 7 extra buttons/LEDs
2020-02-20 [wip] routing MCU expansion headers
2020-02-21 More MCU connections routed
2020-02-21 Even more MCU connections routed
2020-02-23 Routed everything but power
2020-02-23 All connections routed
2020-02-23 Fixed DRC issues
2020-02-25 swap 3.3V supply and 5v led switch. still needs reconnecting and cleanup
2020-02-25 cleaned up audio area, added board version pin
2020-02-28 Added 3d models for encoders and switches
2020-02-29 more power plane cleanup, ARM 10 SWD connector modification for drill clearance
2020-02-29 more power plane routing (untidy)
2020-03-01 power plane finished
2020-03-01 increase some clearances between planes and fix 10-pin samtec PN
2020-03-03 completed board
2020-03-03 minor fixes
2020-03-03 More 3D models
2020-03-03 Remove headset microphone connection
2020-03-03 Flip audio jacks to bottom
2020-03-03 fix RPI3A+ model
2020-03-07 Extend board by 1mm to align ports
2020-03-22 More JLC part numbers added
2020-03-24 Selected all LCSC parts. Check of part numbers complete
2020-03-24 Cleanup silkscreen a lot
2020-03-25 Finish selecting jlc parts
2020-03-25 Board v0.0.0 as ordered
2020-03-31 Fix DAC footprint and other minor issues.
2020-04-17 [wip] skhc switches
2020-04-26 Remove LEDs from main board
2020-04-26 Route SKHC switches
2020-04-27 AUX board design and routing of LEDs
2020-05-25 Fix crystal symbols & Fix audio caps
2020-05-25 Fix jtag resistors
2020-05-27 [AUX] Expand SKHC footprints and move lower keys down
2020-05-29 Screen backlight control (+more)
2020-06-01 3d models
2020-06-01 Add simple front pnael
2020-06-05 Added front panel and shrunk board width
2020-06-07 Added footprint files
2020-06-07 Inserted icons
2020-06-07 add looper and sampler
2020-06-07 add voices
2020-06-09 Added all icons as one big svg
2020-06-09 Final touches on icons
2020-06-10 Moved LEDs closer to buttons
2020-06-10 Inserted button grid on front plate
2020-06-24 Add HEX spacers and fix AUX LED pinouts
2020-06-25 Replace inductors with larger part that is available at jlc
2020-06-25 Generated new gerbers
2020-06-25 Main board v0.1.0 as ordered
2020-07-09 v0.1.0 as ordered
2020-07-15 LEDs Rotated
    All LEDs have had their footprint and board orientation turned 180 degrees, to comply with assembly. Note that the 3rd pin has the marking on the physical part.
2020-07-15 Moved screen header
    Moved screen header to left side of screen.
2020-09-15 Cutouts for mounting frontplate
    Added cutouts to AUX board.
    Frontplate is now the correct size under the following assumptions:
    - 2mm space on left/right side of inner boards to box
    - 5 mm space as above on the front side. This is mainly to allow for insertion (the power switch sticks out)
    - no space on the back side
2020-10-17 Frontplate changes
    Changed icon placement and updated synth, loop, sequencer icons.
    Changed dimensions and added mounting brackets to the frontplate.
2020-10-21 Add step files for main board
2020-10-21 Add rpi step model
2020-10-28 no real change
2020-10-28 Add bracket step files
2020-10-28 Revert "Add bracket step files"
    This reverts commit c21e747328c344bdd5d7dfb352835a19e2e00d67.
2020-10-31 Before 2 designs
    Fix paths for brackets.
    Before splitting into 2 designs for beta test.
2020-11-01 Split to 2 frontplates
    Duplicated frontplate project
    Finished non-copper version
2020-11-01 Finished copper version
    Rebased copper version on finished non-copper version and finished copper version
2020-11-01 Added JLCJLC... text
    Added JLC text to B.Silk for both frontplates
2020-11-05 Changed relief logo
    Now the relief logo is actually a relief
2020-11-05 Added version to silkscreen on frontplates
2020-11-05 v0.2.0 ready for order
2021-01-09 Hardware v0.2.0 as ordered
2021-01-09 Frontpanel changes
2021-01-09 v0.3.0: various aux board fixes
2021-01-11 AUX: kbd key cutouts, screen cutout, H1-H5. Front plate: remove screw hole, mic rings footprint
2021-01-13 Power and battery
2021-01-24 Change all expansion headers to full-size footprints
2021-01-25 FPC header on main board
2021-01-26 MAIN->AUX FPC connector
2021-02-05 Changed 3v3 power circuit
2021-02-28 WIP: routing of power management and new 3V3 IC
2021-02-28 WIP: slight change to previous
2021-02-28 WIP: FPC connector, increase number of lanes. Main board routed
2021-03-05 FPC connector, increase number of lanes. AUX board routed
2021-03-22 Rotated SKHC switches to all be the same rotation
2021-03-22 Fix board connection FPC connector rotation
    Also includes:
    - Slight cleanup of routing on both boards
    - Smaller holes for screws on aux board
2021-03-24 Small adjustments to power button circuit
2021-03-24 Reexport board 3d models
2021-03-24 Restructure projects
    NOTE: Fixes very important bug, where a +5V_REG label in the power circuit
    was misspelled as 5V_REG. Just mentioning in case this commit is reverted
2021-03-24 Smaller Aux board
2021-03-30 Aux v0.3.0
    Small adjustments to PCB outline
    switch to WS2812C LEDs
2021-03-30 Put LEDs on RPI power rail on aux board
2021-03-31 LEDs on PI power on main board
2021-03-31 Front Panel v0.3.0
2021-03-31 Export main board gerbers
2021-05-03 Redesign for STM32F103
2021-12-01 Version 0.3.0 as ordered
2021-12-11 Main board redesign with RP2040
2021-12-12 Rearranged front plate icons
2023-01-15 Update to KiCad 6.0 library
